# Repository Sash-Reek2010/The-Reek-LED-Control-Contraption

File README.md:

# The Reek LED Control Contraption
This project is basically a controller which switches between two different oscillations for two LEDs. One switch leads it to being in constant oscillation between the two circuits. The other switch makes the oscillations creepy and kinda random.\

## The circuit!
This circuit consists of 16 resistors of various resistances, 6 transistors and 4 capacitors of various capacitances as the main parts and then the inputs and outputs. A more detailed list is given in the BOM.
The entire circuit is basically just 3 multivibrators working together! The main bistable circuit acts as the switch that transfers current between the two different oscillation "modes". Then the current triggers a transistor which allows the 5V to pass through an astable circuit. There are two astable circuits with different combinations of resistors and capacitors. The outputs of both the astable circuits lead to two LEDs which provide as the output in this circuit!\

## Try it out!
I made this in the falstad circuit generator! The link is down below.\
https://is.gd/1EUmVZ
## Schematic
The Schematic was made in KiCad!\

## PCB
I decided to make the PCB the shape of the chrome dino with the LEDs as it's eyes. But the dino only has one eye so I just improvised the other one's position!

Thanks for reading! -Sashreek :3

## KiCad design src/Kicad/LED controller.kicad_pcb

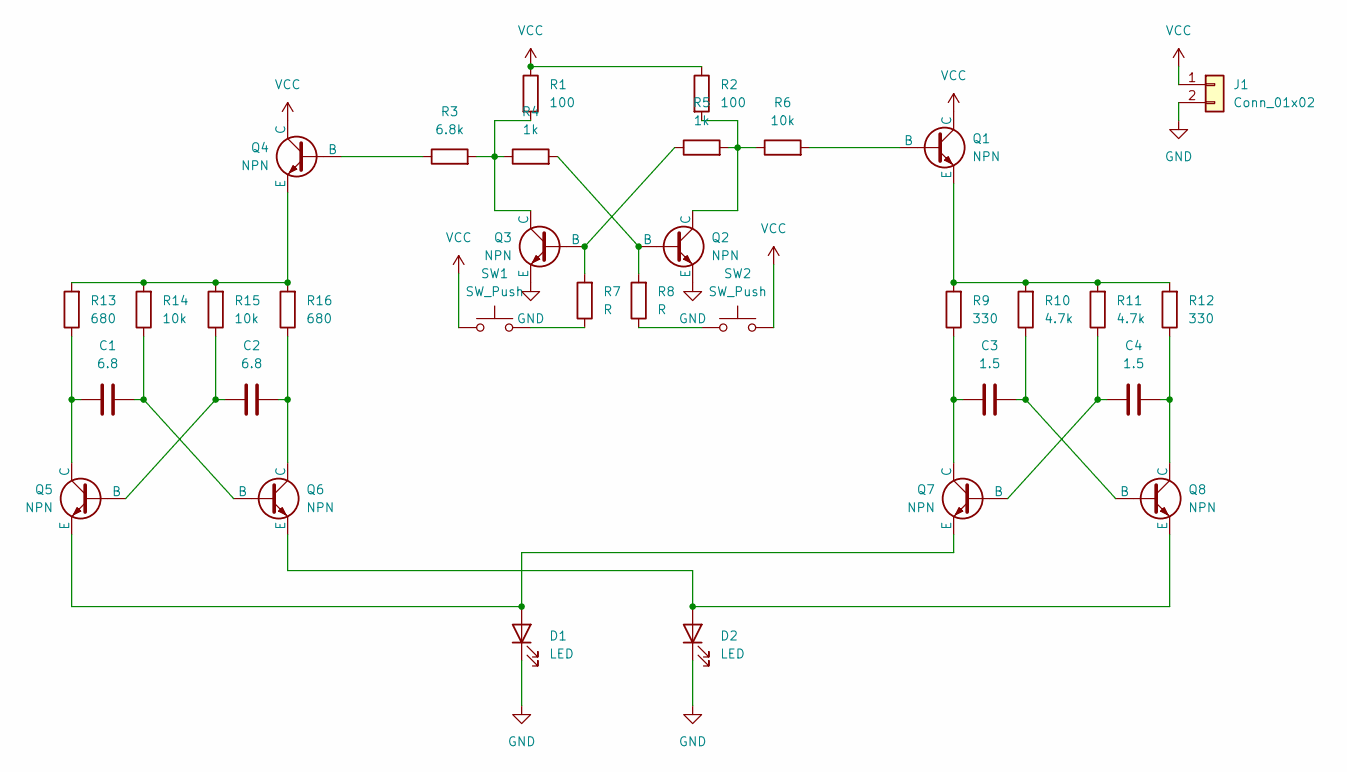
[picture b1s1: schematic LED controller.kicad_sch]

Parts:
C1, C2: 6.8; C_Disc_D5.0mm_W2.5mm_P5.00mm
C3, C4: 1.5; C_Disc_D5.0mm_W2.5mm_P5.00mm
D1, D2: LED; LED_D5.0mm
J1: Conn_01x02; PinHeader_1x02_P2.54mm_Vertical
Q1, Q2, Q3, Q4, Q5, Q6, Q7, Q8: NPN; TO-92L_Inline_Wide
R1, R2: 100; R_Axial_DIN0204_L3.6mm_D1.6mm_P7.62mm_Horizontal
R3: 6.8k; R_Axial_DIN0204_L3.6mm_D1.6mm_P7.62mm_Horizontal
R4, R5: 1k; R_Axial_DIN0204_L3.6mm_D1.6mm_P7.62mm_Horizontal
R6, R14, R15: 10k; R_Axial_DIN0204_L3.6mm_D1.6mm_P7.62mm_Horizontal
R7, R8: R; R_Axial_DIN0204_L3.6mm_D1.6mm_P7.62mm_Horizontal
R9, R12: 330; R_Axial_DIN0204_L3.6mm_D1.6mm_P7.62mm_Horizontal
R10, R11: 4.7k; R_Axial_DIN0204_L3.6mm_D1.6mm_P7.62mm_Horizontal
R13, R16: 680; R_Axial_DIN0204_L3.6mm_D1.6mm_P7.62mm_Horizontal
SW1, SW2: SW_Push; SW_PUSH_6mm

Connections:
GND: D1.1 (K), D2.1 (K), J1.2, Q2.3 (E), Q3.3 (E)
unnamed: D1.2 (A), Q5.3 (E), Q7.3 (E)
unnamed: D2.2 (A), Q6.3 (E), Q8.3 (E)
unnamed: Q1.2 (B), R6.2
unnamed: Q1.3 (E), R9.2, R10.2, R11.2, R12.2
unnamed: Q2.2 (B), R4.2, R8.2
unnamed: Q2.1 (C), R2.2, R5.2, R6.1
unnamed: Q3.2 (B), R5.1, R7.2
unnamed: Q3.1 (C), R1.2, R3.2, R4.1
unnamed: Q4.2 (B), R3.1
unnamed: Q4.3 (E), R13.2, R14.2, R15.2, R16.2
unnamed: C2.1, Q5.2 (B), R15.1
unnamed: C1.1, Q5.1 (C), R13.1
unnamed: C1.2, Q6.2 (B), R14.1
unnamed: C2.2, Q6.1 (C), R16.1
unnamed: C4.1, Q7.2 (B), R11.1
unnamed: C3.1, Q7.1 (C), R9.1
unnamed: C3.2, Q8.2 (B), R10.1
unnamed: C4.2, Q8.1 (C), R12.1
unnamed: R7.1, SW1.2
unnamed: R8.1, SW2.1
VCC: J1.1, Q1.1 (C), Q4.1 (C), R1.1, R2.1, SW1.1, SW2.2

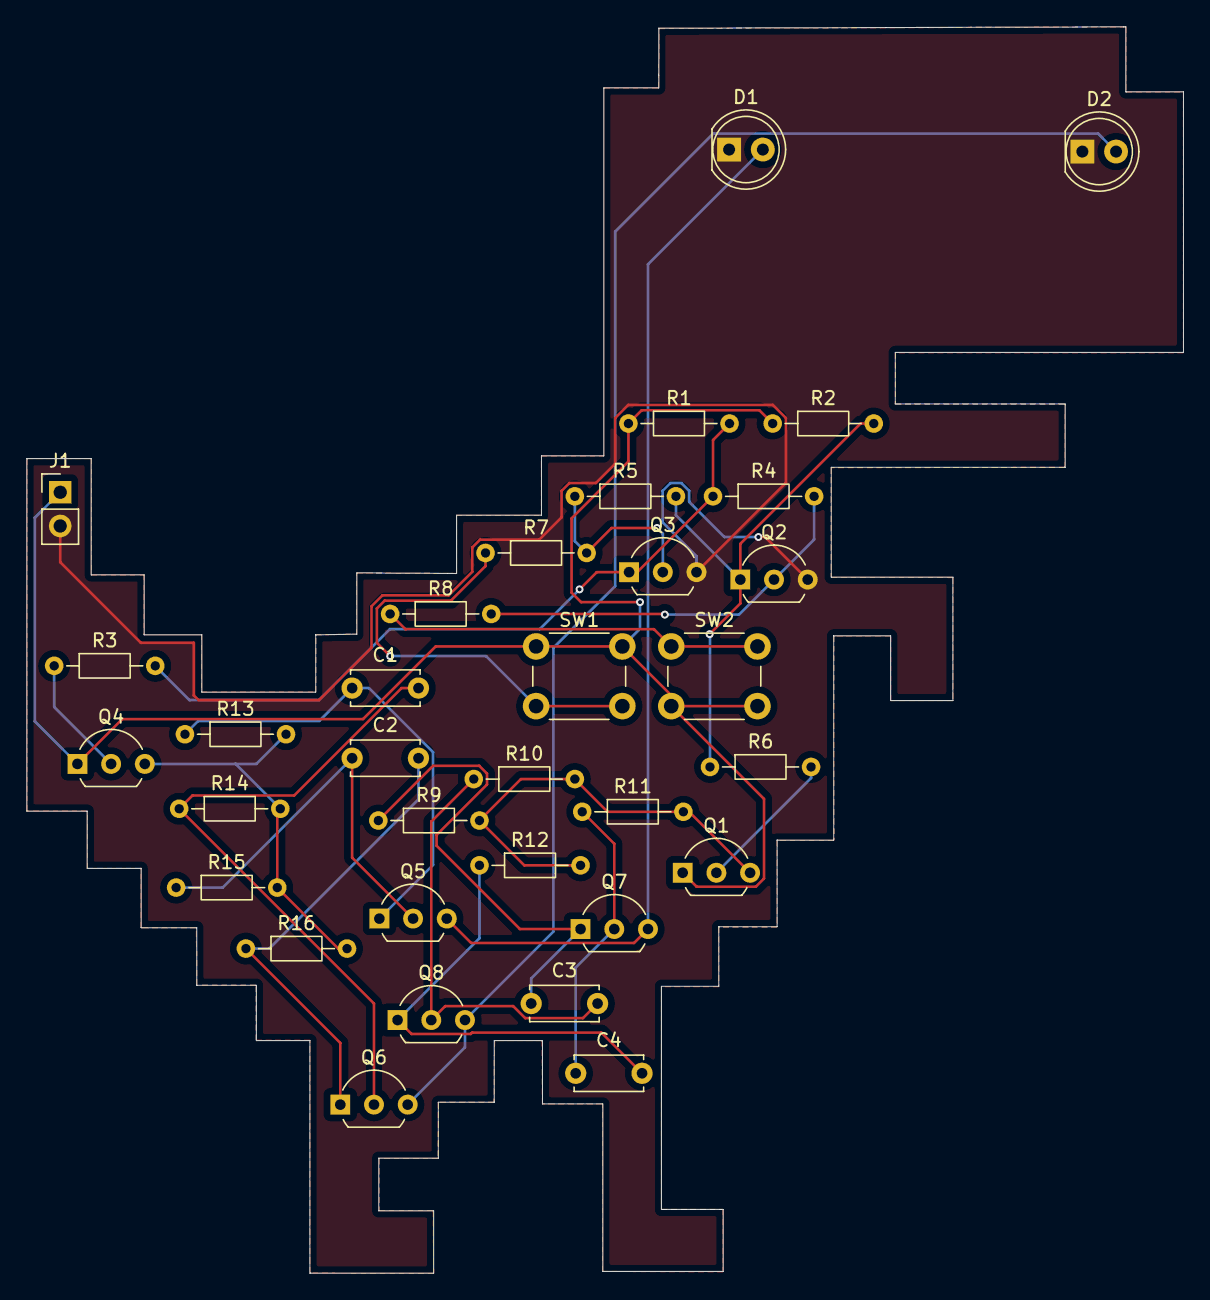
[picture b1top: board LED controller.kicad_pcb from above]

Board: 2 copper layers, 87.2 x 93.9 mm, 33 parts (0 on the bottom side), 22 nets.
